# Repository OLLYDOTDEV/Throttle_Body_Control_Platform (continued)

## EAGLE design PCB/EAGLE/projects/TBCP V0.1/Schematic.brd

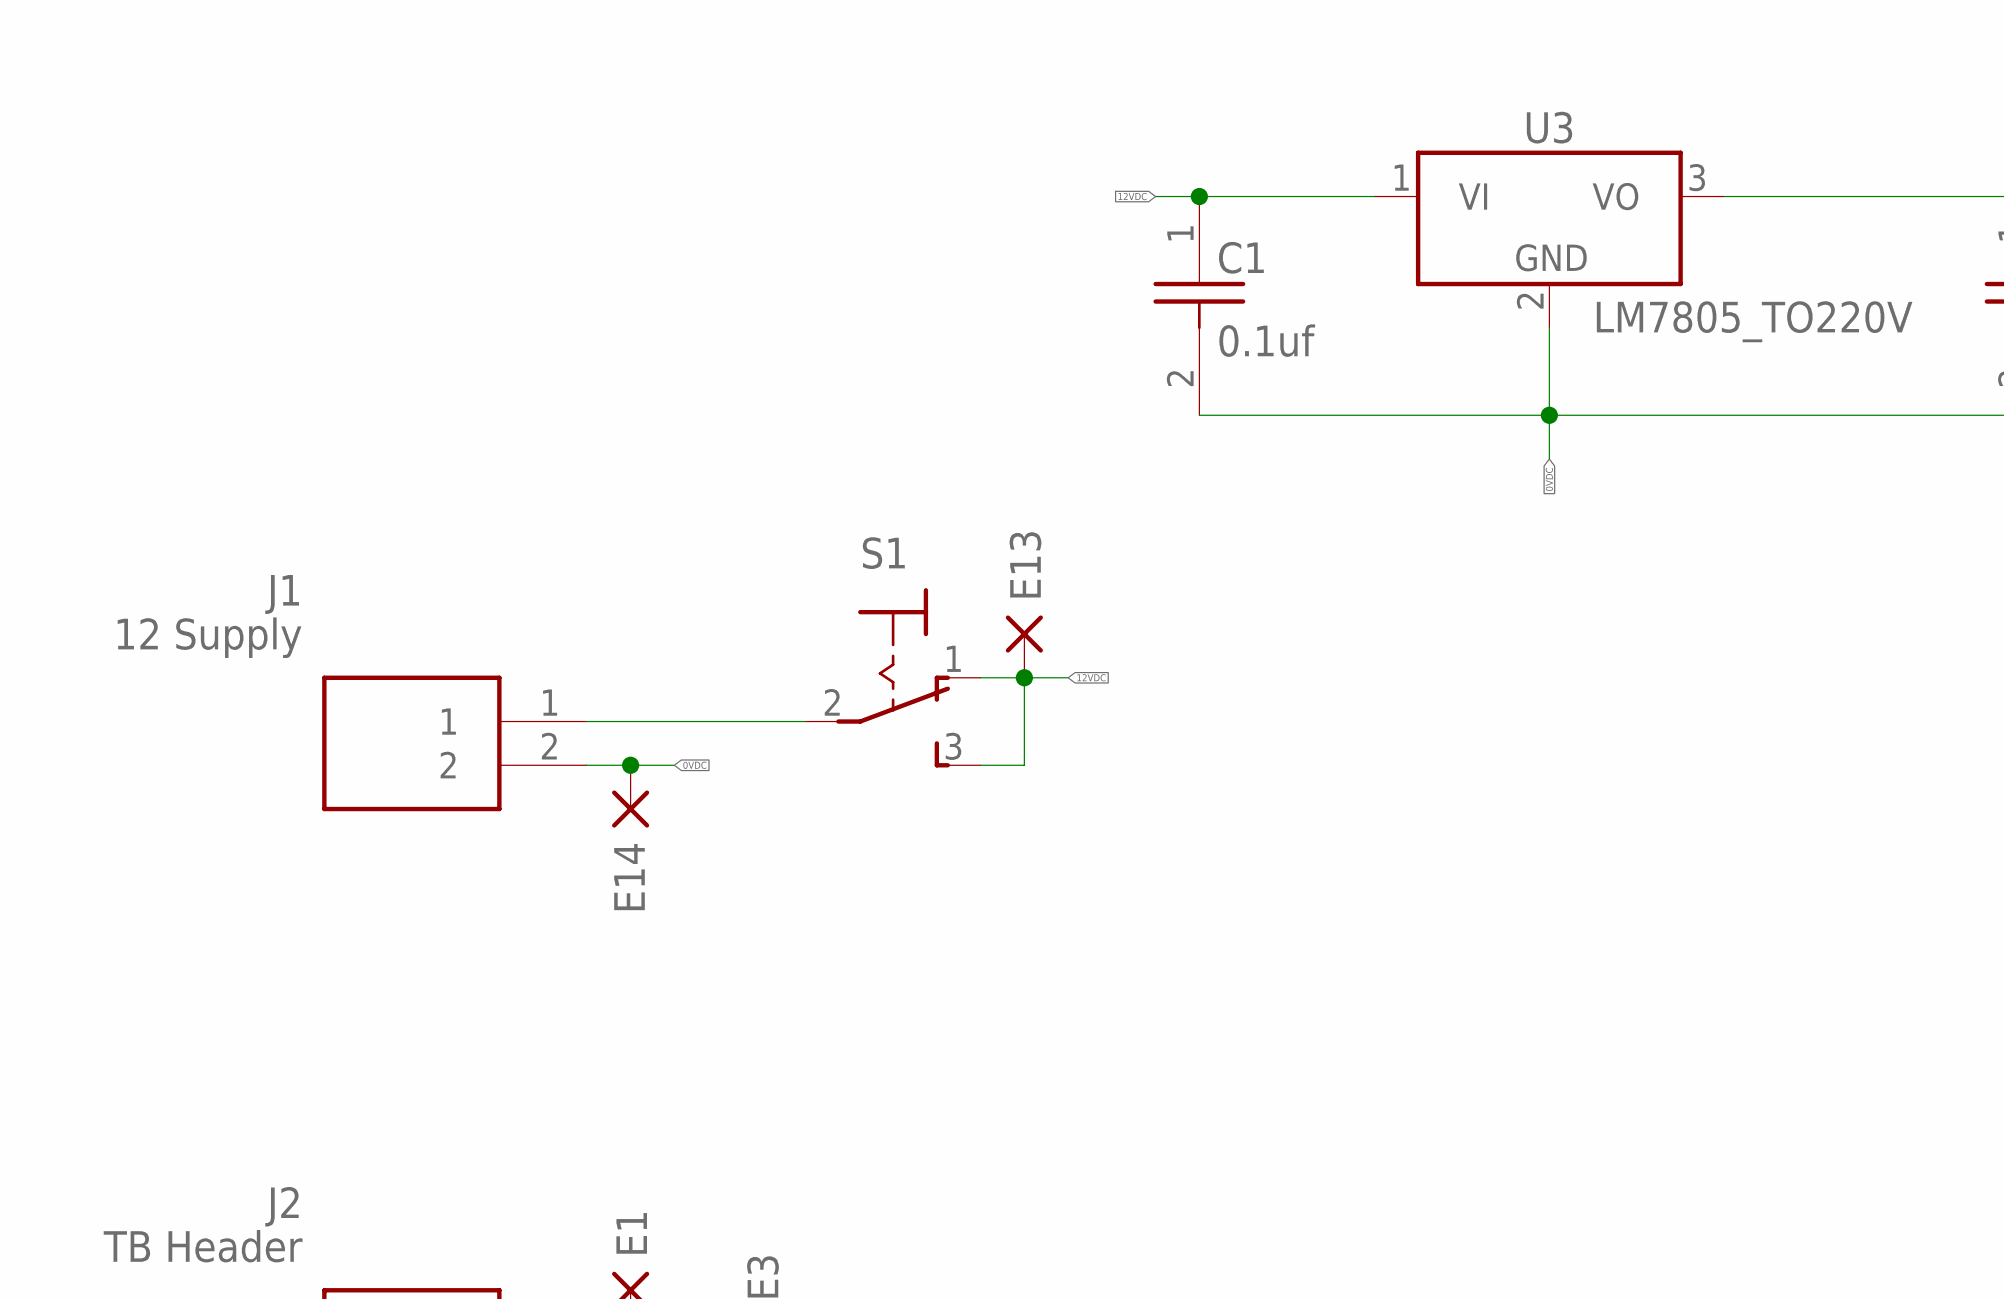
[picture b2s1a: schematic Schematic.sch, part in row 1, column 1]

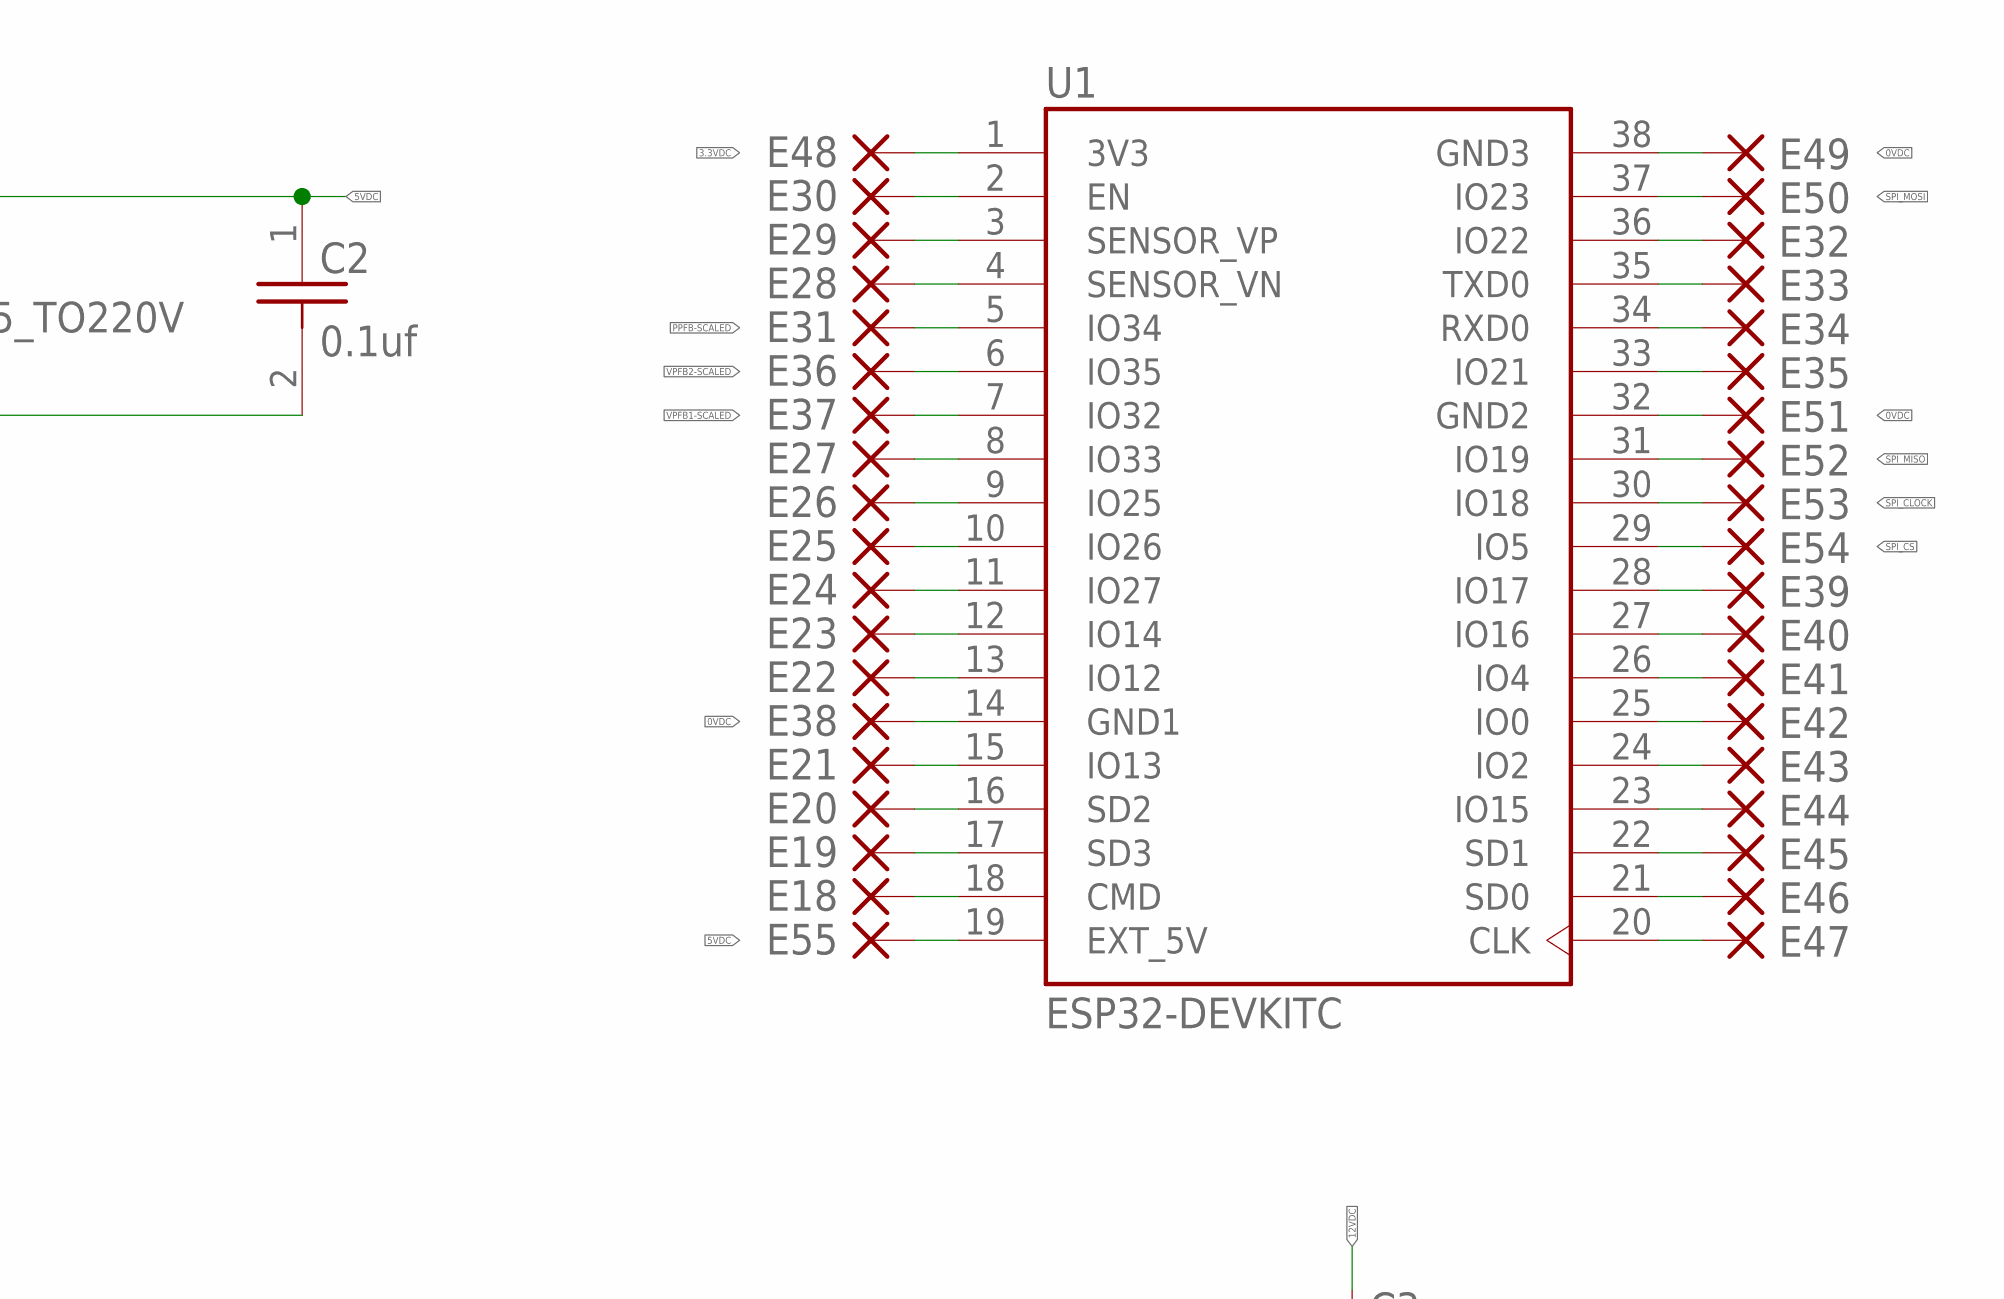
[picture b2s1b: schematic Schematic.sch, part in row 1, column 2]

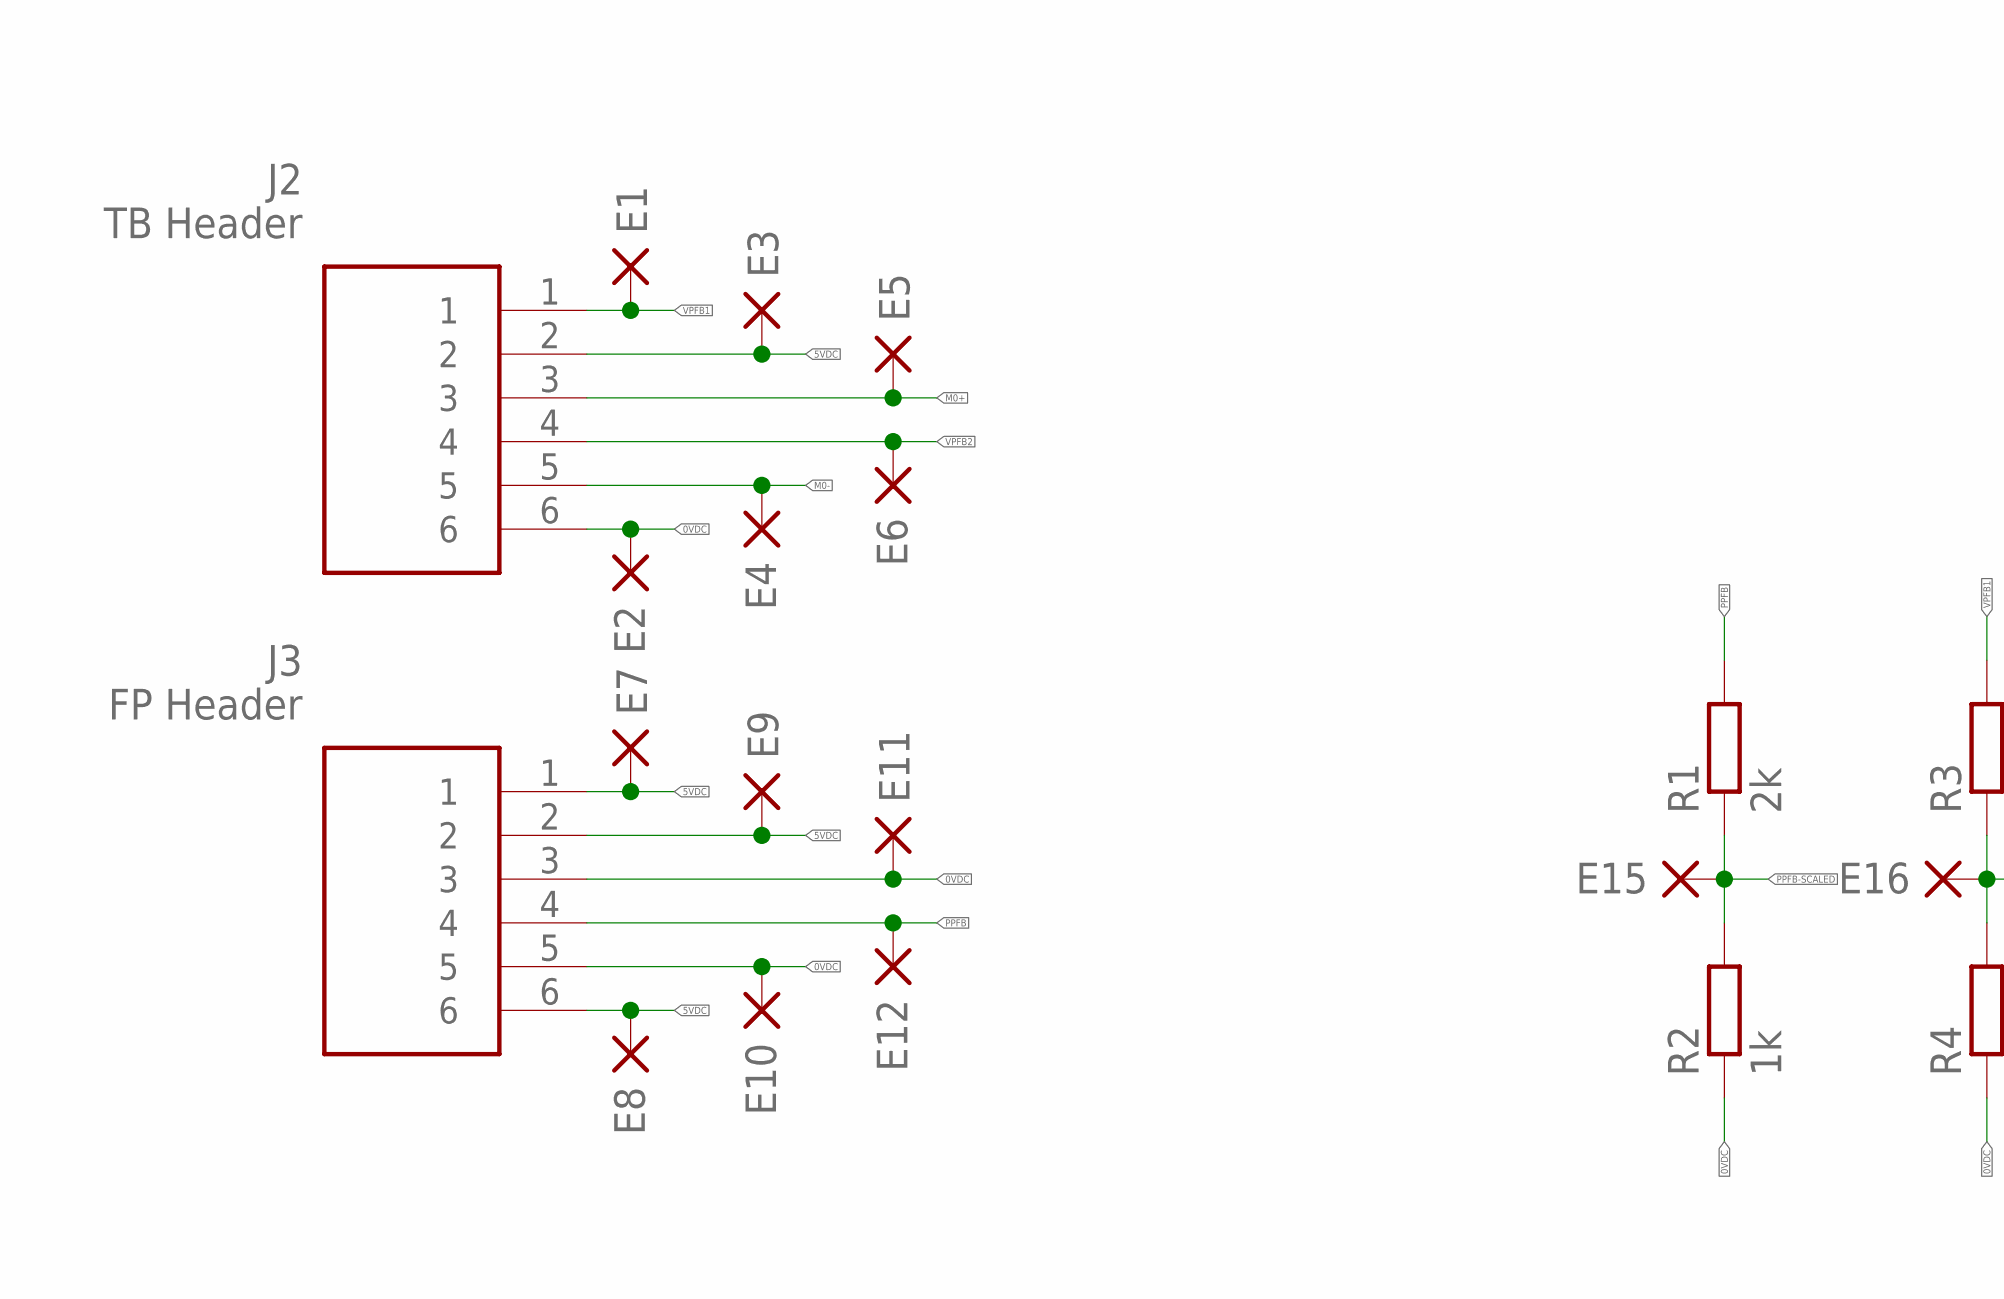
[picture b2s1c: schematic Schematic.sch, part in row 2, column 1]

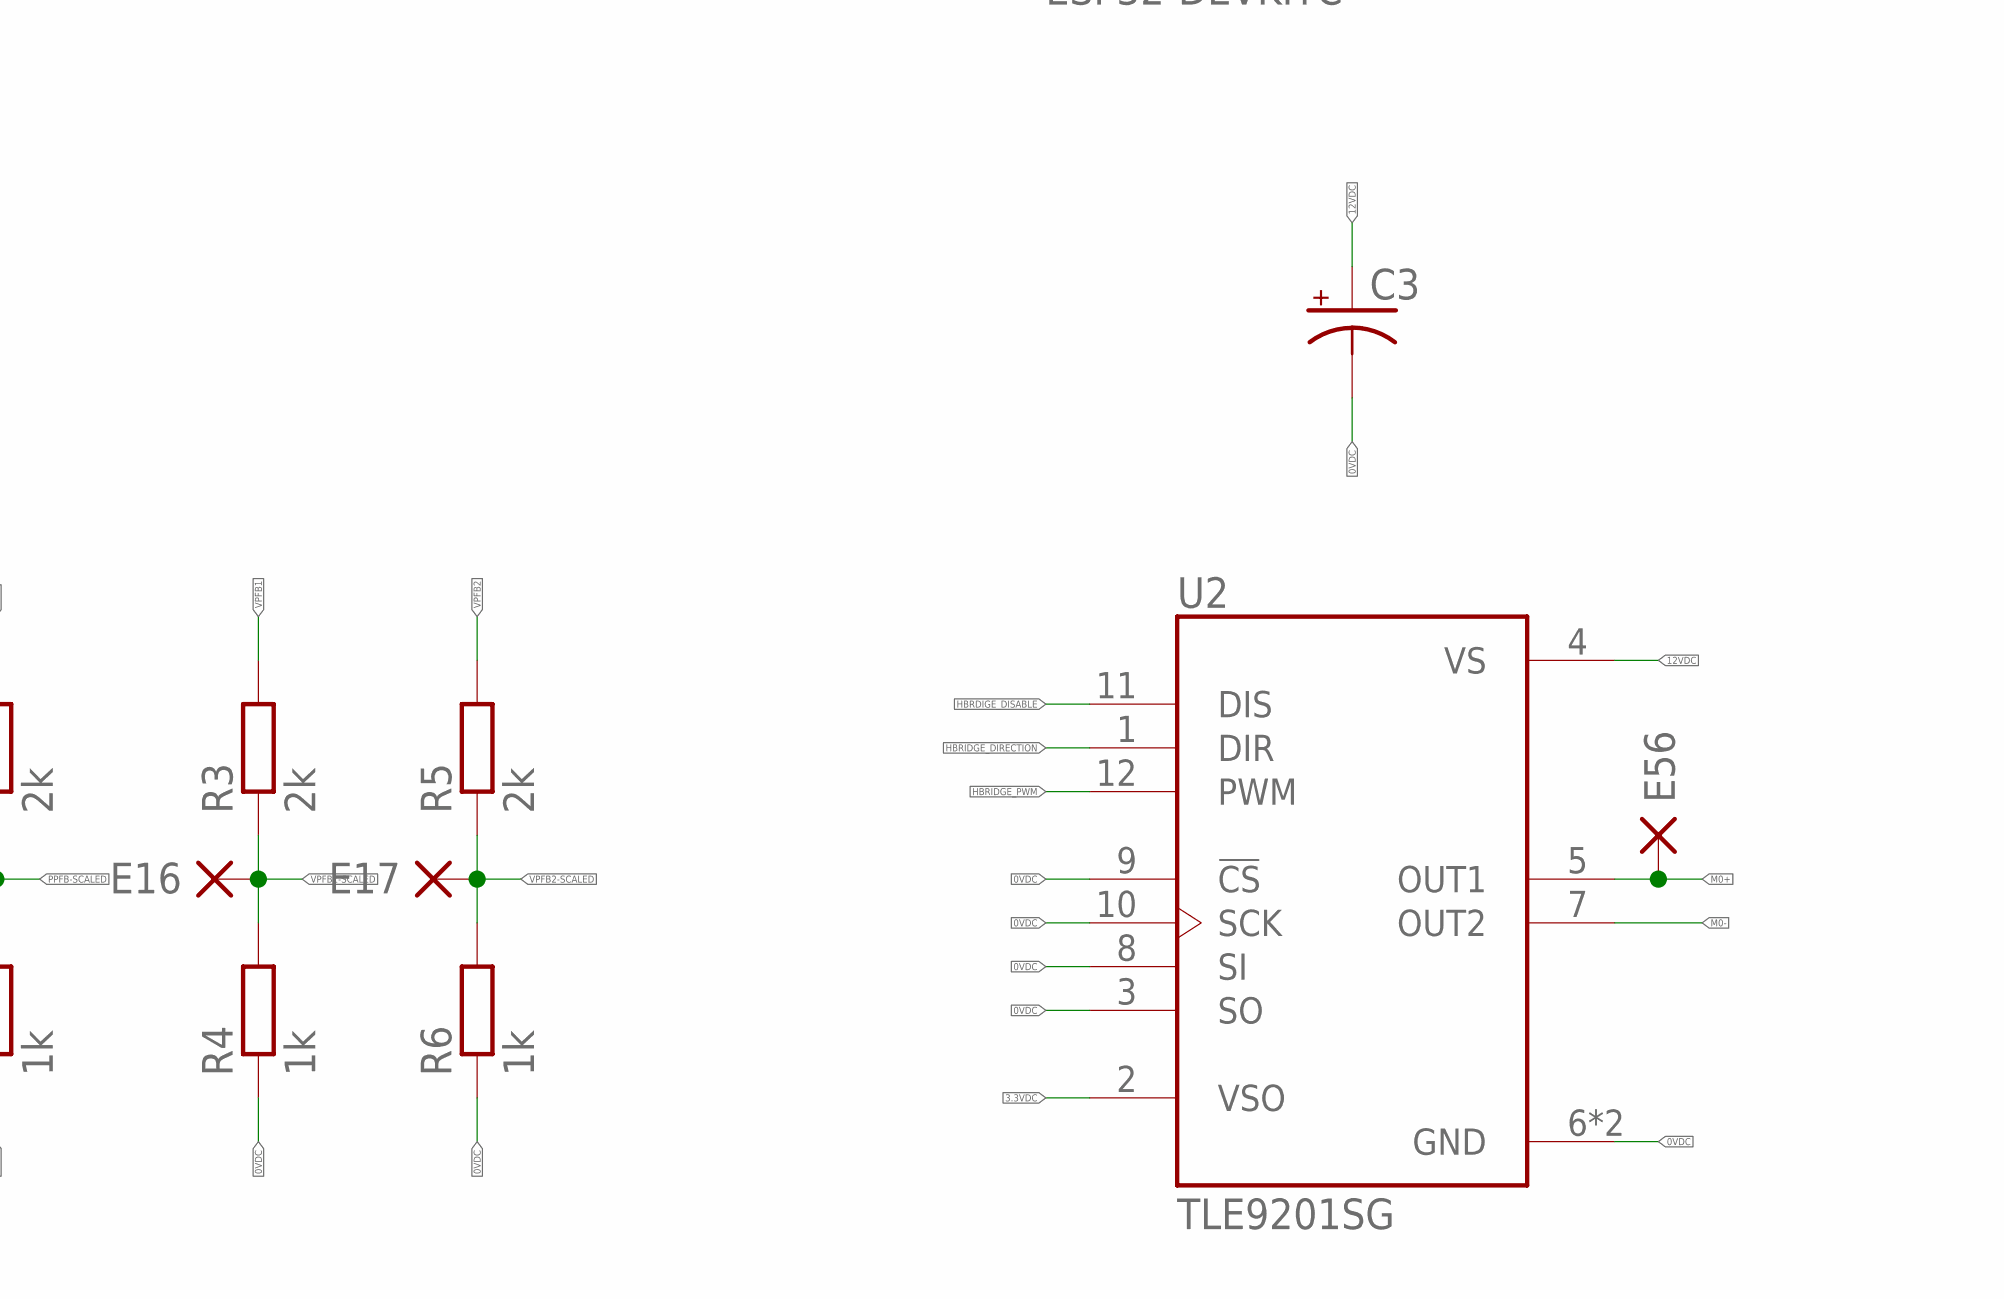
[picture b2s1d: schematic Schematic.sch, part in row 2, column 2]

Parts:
C1, C2: 0.1uf; CAPRR254W51L508T318H635P
C3: CAPACITOR-PE3.5-8; E3,5-8
E1, E2, E3, E4, E5, E6, E7, E8, E9, E10, E11, E12, E13, E14, E15, E16, E17, E18, E19, E20, E21, E22, E23, E24, E25, E26, E27, E28, E29, E30, E31, E32, E33, E34, E35, E36, E37, E38, E39, E40, E41, E42, E43, E44, E45, E46, E47, E48, E49, E50, E51, E52, E53, E54, E55, E56: DPADS_PAD-0400-S; DPADS_0400-S
J1: 12 Supply; 1757284
J2: TB Header; 1757284
J3: FP Header; 1757284
R1, R3, R5: 2k; 0207/10
R2, R4, R6: 1k; 0207/10
S1: 320-916
U1: ESP32-DEVKITC; MODULE_ESP32-DEVKITC
U2: TLE9201SG; IC_TLE9201SG
U3: LM7805_TO220V; TO220V

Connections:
0VDC: C1.2, C2.2, C3.-, E2.PAD, E10.PAD, E11.PAD, E14.PAD, E38.PAD, E49.PAD, E51.PAD, J1.2, J2.6, J3.3, J3.5, R2.1, R4.1, R6.1, U1.14 (GND1), U1.32 (GND2), U1.38 (GND3), U2.3 (SO), U2.6 (GND), U2.8 (SI), U2.9 (!CS), U2.10 (SCK), U2.13 (GND), U3.2 (GND)
3.3VDC: E48.PAD, U1.1 (3V3), U2.2 (VSO)
5VDC: C2.1, E3.PAD, E7.PAD, E8.PAD, E9.PAD, E55.PAD, J2.2, J3.1, J3.2, J3.6, U1.19 (EXT_5V), U3.3 (VO)
12VDC: C1.1, C3.+, E13.PAD, S1.1 (O), U2.4 (VS), U3.1 (VI)
HBRDIGE_DISABLE: E41.PAD, U1.26 (IO4), U2.11 (DIS)
HBRIDGE_DIRECTION: E42.PAD, U1.25 (IO0), U2.1 (DIR)
HBRIDGE_PWM: E43.PAD, U1.24 (IO2), U2.12 (PWM)
M0+: E5.PAD, E56.PAD, J2.3, U2.5 (OUT1)
M0-: E4.PAD, J2.5, U2.7 (OUT2)
unnamed: J1.1, S1.2
unnamed: E32.PAD, U1.36 (IO22)
unnamed: E33.PAD, U1.35 (TXD0)
unnamed: E34.PAD, U1.34 (RXD0)
unnamed: E35.PAD, U1.33 (IO21)
unnamed: E39.PAD, U1.28 (IO17)
unnamed: E40.PAD, U1.27 (IO16)
unnamed: E44.PAD, U1.23 (IO15)
unnamed: E45.PAD, U1.22 (SD1)
unnamed: E46.PAD, U1.21 (SD0)
unnamed: E47.PAD, U1.20 (CLK)
unnamed: E30.PAD, U1.2 (EN)
unnamed: E29.PAD, U1.3 (SENSOR_VP)
unnamed: E28.PAD, U1.4 (SENSOR_VN)
unnamed: E27.PAD, U1.8 (IO33)
unnamed: E26.PAD, U1.9 (IO25)
unnamed: E25.PAD, U1.10 (IO26)
unnamed: E24.PAD, U1.11 (IO27)
unnamed: E23.PAD, U1.12 (IO14)
unnamed: E22.PAD, U1.13 (IO12)
unnamed: E21.PAD, U1.15 (IO13)
unnamed: E20.PAD, U1.16 (SD2)
unnamed: E19.PAD, U1.17 (SD3)
unnamed: E18.PAD, U1.18 (CMD)
PPFB: E12.PAD, J3.4, R1.2
PPFB-SCALED: E15.PAD, E31.PAD, R1.1, R2.2, U1.5 (IO34)
SPI_CLOCK: E53.PAD, U1.30 (IO18)
SPI_CS: E54.PAD, U1.29 (IO5)
SPI_MISO: E52.PAD, U1.31 (IO19)
SPI_MOSI: E50.PAD, U1.37 (IO23)
VPFB1: E1.PAD, J2.1, R3.2
VPFB1-SCALED: E16.PAD, E37.PAD, R3.1, R4.2, U1.7 (IO32)
VPFB2: E6.PAD, J2.4, R5.2
VPFB2-SCALED: E17.PAD, E36.PAD, R5.1, R6.2, U1.6 (IO35)

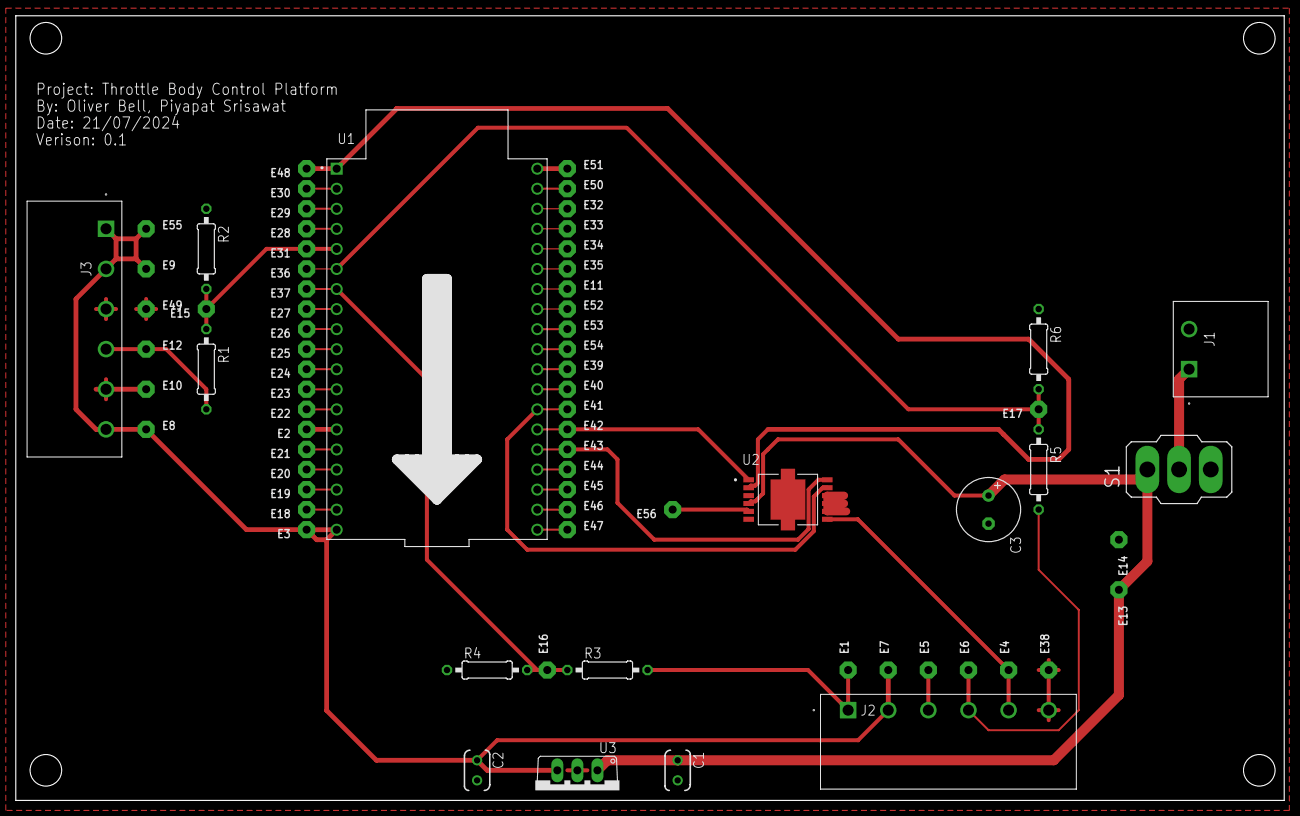
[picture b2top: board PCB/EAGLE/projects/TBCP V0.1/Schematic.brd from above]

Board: 2 copper layers, 160.6 x 99.4 mm, 72 parts (0 on the bottom side), 43 nets.

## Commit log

2024-04-04 Add .whitesource configuration file
2024-04-04 New folders
    Created key folder structures
2024-04-05 Added library
    - ESP32 Wroom .lib
    - H bridge IC (TLE9201SG) .lib
2024-04-05 Added README.MD
    Readme is populated by content of the 1 page proposal
2024-04-05 Initial file move
    Moving files that existed before this repo was setup .
2024-04-11 folder changes
    Updated project structure
2024-04-11 upload
2024-04-11 test file
2024-04-11 Removed test file
2024-04-11 Platform IO
    Started with swapping project over to using PLATFORM IO as a test.
2024-04-12 Serial Studio example project - Working prototype
    Finished the first version of the Code to create the data frames for Serial Studio for both modes
2024-04-12 ArduinoJson - Dependences removed
    - StaticJsonDocument<256> doc;
    + JsonDocument doc;
    as per
    https://arduinojson.org/news/2024/01/03/arduinojson-7/
    to allow for on going support
2024-06-05 Initial Schematics
    Start with Schematics in eagle cad and other small changes
2024-06-11 TBCP V0 - first complete PCB
    All PCB traces routed and schematics ready for review
2024-06-12 Name change
    Updated IC1 to U3
2024-06-12 Exported PDF
    - Exported PDF of both the PCB and design
2024-06-28 Setup Matlab into R&D
    - Changed folder structure.
    - Added Provided Simlink Models
2024-06-28 Add model callback
    Added callback to ensure settings variables are loaded into mem on model load
2024-06-29 Removed duplicate files
    Files that were thought to be from connor's projects were duplicate files
2024-07-11 test
    test
2024-07-12 Add-on List
2024-07-15 Added Connor work
    contains Simlink models with support for hardware and simulation from the previous project
2024-07-15 Move File
2024-07-16 Removed SLPRJ
    old unneeded file
2024-07-16 Setup TB Test
    Create new test project dir
2024-07-17 PCB TBCP V0.1
    Created TBCP V0.1 with covers the initial mistakes found in V0
2024-07-17 Renamed R&D Folder
2024-07-17 Working Test code
    TB Test currently supports TBCP V0
2024-07-19 non scaled proportional control added
    Working test code that directly maps the food pedal input to the position of the throttle body
2024-07-20 Implemented PID control
    Added Basic PID control to the test code
2024-07-20 added SS JSON
2024-07-20 Fix's to TBCP V0.1 hardware
2024-07-21 Started TBCP V2
2024-07-22 ADS1115 Interface
    First attempt at a Simulink interface for a ADS1115 IC
2024-07-22 Tests for RPI Block with arduino
2024-07-22 Relocated Files
2024-07-23 A clean working state for ADS1115
2024-07-25 testing
2024-07-27 TBCP 2.0 Board layout half done
2024-07-28 Added Serial Studio for TB test
2024-07-29 S function Still not working
2024-07-30 TCBP 2.0 almost ready
    Just need to double check for errors
2024-07-30 Simulation
2024-07-31 TBCP 2.0 for review
2024-08-01 Major rename of folder
    matlab doesnt like have spaces in names of files or folders
2024-08-01 Test backup as per email to matlab
2024-08-01 TBCP 2.0 sent to JLCPCB
2024-08-02 ADS1115 interface with simulink working
2024-08-02 Implemented gain selection
    gain for PGA within ADC how can be selected by the block parameter
2024-08-02 Fixed time scale
2024-08-02 Fix to V3 for ADC1115
2024-08-02 Updated ADS1115 #include
2024-08-03 NYE_ADC1115
2024-08-03 ADS1115 updated to check current DIR
2024-08-03 LEDC PWM For Simulink added
2024-08-03 Removed Extra lines for LEDCI
2024-08-03 Updated LEDCI to support currentDir
2024-08-03 Added custom analog read for ESP32
2024-08-05 Added 3d Models to headers
2024-08-05 Added ESP32 simulink muliblock analog read
2024-08-06 CONTROL_SYSTEM
2024-08-08 All PCB parts now updated to have 3D models
2024-08-09 Toggle Latch
2024-08-17 Added First Case Prototype
2024-08-19 Case Fit Calibration V4.stl
    Test files to test the fit between parts
2024-08-19 Control testing
2024-08-19 Advance control
2024-08-20 Started Master project for Bottem Shell
2024-08-20 Started Shell bottom master 3d print file
2024-08-21 changer to shell master
2024-08-28 A3 Schematic pdf
2024-09-17 Added A1 PDF
2024-09-17 Added electrical schematic SVG
2024-11-03 Control Change
2024-11-10 Moved a copy of the control system to V3
2024-11-10 moved to V4
2024-11-10 test
2024-11-10 file copy
2024-11-11 Added 3d Models step files
2024-11-11 removed outdated copy's of old files
2024-11-11 [ImgBot] Optimize images
    *Total -- 4,956.53kb -> 3,980.03kb (19.7%)
    /CODE/Main/Control_System_V3/LED.png -- 32.21kb -> 12.95kb (59.79%)
    /CODE/Research_And_Development/Matlab/Control_System_V3_k/LED.png -- 32.21kb -> 12.95kb (59.79%)
    /CODE/Main/Control_System_V3/Waring.png -- 30.60kb -> 12.84kb (58.03%)
    /CODE/Research_And_Development/Matlab/Control_System_V3_k/Waring.png -- 30.60kb -> 12.84kb (58.03%)
    /PCB/EAGLE/projects/TBCP V2/Schematic.png -- 239.74kb -> 104.15kb (56.56%)
2024-11-11 Project Tracking
2024-11-13 graph resutls
2025-10-18 Final
